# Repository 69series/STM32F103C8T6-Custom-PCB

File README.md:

# STM32F103C8T6 Custom PCB

A custom-designed 2-layer development board built around the STM32F103C8T6 (Arm Cortex-M3), featuring USB, UART, I2C, and SWD interfaces. Designed from schematic to manufacturing files in KiCad, inspired by Phil's Lab's PCB design tutorials.

## Table of Contents

- [Overview](#overview)
- [Features](#features)
- [Schematic](#schematic)
- [PCB Layout](#pcb-layout)
- [Pin Configuration](#pin-configuration)
- [Programming the Board](#programming-the-board)
- [Bill of Materials](#bill-of-materials)
- [Manufacturing Files](#manufacturing-files)
- [Design Decisions](#design-decisions)
- [Future Improvements](#future-improvements)
- [License](#license)

## Overview

This repository documents the complete design process of a custom STM32F103C8T6-based PCB, from schematic capture through PCB layout to manufacturing-ready Gerber files. The project was built as a hands-on learning exercise in embedded hardware design, covering power regulation, USB connectivity, debug/programming interfaces, and signal integrity considerations on a 2-layer board.

## Features

- **MCU:** STM32F103C8T6 (Arm Cortex-M3, 72MHz, 64KB Flash, 20KB RAM)
- **USB 2.0 Full-Speed** connectivity via onboard Micro USB-B connector
- **Three programming/flashing methods:**
  - SWD (Serial Wire Debug) via ST-Link for flashing + live debugging
  - UART bootloader (via broken-out USART1 header)
  - USB DFU bootloader (native USB, no extra hardware required)
- **I2C2 interface** broken out via header for external sensors/peripherals
- **UART1 interface** broken out via header for serial communication/debugging
- **Manual BOOT0 selector switch** for toggling between application and bootloader mode
- **Onboard 3.3V regulation** via AMS1117-3.3 LDO from USB VBUS
- **16MHz crystal oscillator** with calculated load capacitance for accurate clock generation
- **Dedicated analog supply (VDDA)** isolated via ferrite bead for clean ADC performance
- **Solid ground plane** (bottom layer) with thermal-relief pad connections for reliable hand-soldering
- **4x mounting holes** for enclosure/standoff compatibility

## Schematic

The schematic is organized into four functional blocks: power supply, microcontroller core, USB circuitry, and external interface headers.

### Power Supply

- VBAT and all VDD pins are individually decoupled with 100nF capacitors, placed close to each pin to minimize trace inductance and provide a low-impedance path for high-frequency switching noise.
- A 10µF bulk capacitor sits in parallel to handle larger transient current demands.
- VDDA (analog supply) is isolated from the digital 3.3V rail using a 120Ω ferrite bead, preventing digital switching noise from corrupting ADC readings. Three additional decoupling capacitors support this analog rail.
- A AMS1117-3.3 LDO regulates incoming USB VBUS (5V) down to a clean 3.3V rail for the entire board.

### Reset and Boot Configuration

- **NRST** is decoupled with a 100nF capacitor to filter transient noise; no manual reset switch is present in this revision (see [Future Improvements](#future-improvements)).
- **BOOT0** is pulled low through a 10kΩ resistor by default (normal application boot), with a SPDT switch (SW1) allowing manual selection of bootloader mode for flashing.

### Oscillator

- A 16MHz crystal (Y1) provides the system clock, with load capacitors (C10, C11) calculated from the crystal's specified load capacitance, accounting for PCB trace and pin stray capacitance.

### Communication Interfaces

- **USART1** broken out to a 4-pin header (GND, RX, TX, 3.3V) for general-purpose serial communication.
- **I2C2** (SCL/SDA) broken out to a 4-pin header, with 1.5kΩ pull-up resistors on both lines (required since I2C is an open-drain bus).

### USB Circuitry

- Micro USB-B connector provides VBUS for power and D+/D- for USB Full-Speed data.
- D+ is pulled high through a 1.5kΩ resistor, signaling to the host that this is a Full-Speed USB device during enumeration.

### Debug Interface

- SWD (SWDIO, SWCLK) broken out to a 4-pin header (GND, CLK, IO, 3.3V) for programming and live debugging via ST-Link.

## PCB Layout

The board is a 2-layer design (F.Cu / B.Cu) measuring 41.5mm x 33mm, laid out in KiCad.

### Layer Stack

| Layer | Purpose |
|---|---|
| F.Cu (Top) | Signal routing, component placement |
| B.Cu (Bottom) | Solid ground plane (filled zone) |

### Trace Widths

| Net Type | Width | Rationale |
|---|---|---|
| Signal (I2C, UART, GPIO) | 0.3mm | Standard for logic-level signals; current is negligible, width chosen for routability |
| Power / Ground | 0.5mm | Comfortable margin above required ampacity (board draws well under 200mA) |

### Ground Plane Configuration

- **Fill zone:** B.Cu layer, solid ground pour
- **Clearance:** 0.3mm
- **Minimum width:** 0.25mm
- **Pad connection:** Thermal relief (both gap and spoke width = 0.5mm) — chosen over solid/direct connection to keep pads hand-solderable without excessive heat sinking into the copper pour

### Via Sizing

- **Standard vias:** 0.7mm
- **3.3V power vias:** 0.75mm

Via sizes were chosen conservatively (larger than minimum fab capability) to prioritize manufacturing reliability and ease of hand-soldering/rework over board density, appropriate for a learning-focused first PCB project.

### Layout Considerations

- **UART and USB separation:** USART1 was deliberately routed to the top-side header (PB6/PB7) rather than its default pins (PA9/PA10), which sit immediately adjacent to the USB D+/D- lines (PA11/PA12). This reduces the risk of crosstalk between the UART signals and the USB differential pair.
- **Decoupling capacitor placement:** All decoupling capacitors are placed as close as possible to their respective VDD/VSS pin pairs to minimize loop inductance.
- **USB differential pair routing:** D+/D- are routed as a tight, closely-coupled pair into the host detection pull-up network before reaching the MCU.
- **Regulator copper area:** The AMS1117 (U2) is given adjacent copper pour on the 3.3V net to assist with passive heat dissipation.

## Pin Configuration

| Function | Pin(s) | Notes |
|---|---|---|
| USART1 (TX/RX) | PB6 (TX), PB7 (RX) | Moved from default PA9/PA10 to avoid proximity to USB lines |
| I2C2 (SCL/SDA) | PB10 (SCL), PB11 (SDA) | 1.5kΩ pull-ups on both lines |
| USB | PA11 (D-), PA12 (D+) | D+ pulled high via 1.5kΩ for Full-Speed device detection |
| SWD | PA13 (SWDIO), PA14 (SWCLK) | Programming and debugging via ST-Link |
| BOOT0 | Pin 44 | Pulled low via 10kΩ by default; SPDT switch allows manual high selection |
| NRST | Pin 7 | Decoupled with 100nF capacitor; no manual reset switch in this revision |
| OSC_IN / OSC_OUT | PD0, PD1 | 16MHz external crystal with calculated load capacitors |
| VDD / VSS | Multiple pins | Individually decoupled with 100nF capacitors + 10µF bulk capacitor |
| VDDA / VSSA | Analog supply pins | Isolated via 120Ω ferrite bead from digital 3.3V rail |

## Programming the Board

This board supports three independent methods for flashing firmware, offering flexibility depending on available hardware.

### Method 1: SWD (recommended for development)

**Requires:** ST-Link V2 programmer/debugger

1. Connect ST-Link to the SWD header (GND, CLK, IO, 3.3V)
2. Flash and debug directly from STM32CubeIDE, or via STM32CubeProgrammer
3. Supports full live debugging — breakpoints, register/variable inspection, step execution

This is the only method that supports real-time debugging, not just flashing.

### Method 2: UART Bootloader

**Requires:** USB-to-TTL serial adapter

1. Set **BOOT0 = HIGH** using SW1
2. Connect the adapter to the UART1 header (GND, RX, TX, 3.3V) — cross TX/RX between board and adapter
3. Power cycle the board (no manual reset switch in this revision)
4. Flash using STM32CubeProgrammer (UART connection mode) or compatible tools
5. Set **BOOT0 = LOW**, power cycle again to boot the new application

### Method 3: USB DFU Bootloader

**Requires:** Micro USB-B cable only (no extra hardware)

1. Set **BOOT0 = HIGH** using SW1
2. Connect the board via USB — it enumerates as a DFU device
3. **Windows only:** install a WinUSB driver using [Zadig](https://zadig.akeo.ie/) (one-time setup)
4. Flash using `dfu-util` or STM32CubeProgrammer (USB connection mode):
`dfu-util -a 0 -s 0x08000000:leave -D firmware.bin`
5. Set **BOOT0 = LOW**, power cycle to boot the new application

> **Note:** Unlike boards with an onboard USB-to-serial bridge (e.g. ESP32 dev boards), this design requires manual BOOT0/reset toggling for every flash cycle, since there is no automatic reset circuitry. See [Future Improvements](#future-improvements) for a planned revision addressing this.

## Bill of Materials

| Ref | Qty | Value / Part | Footprint | Description |
|---|---|---|---|---|
| U1 | 1 | STM32F103C8T6 | LQFP-48, 7x7mm, 0.5mm pitch | Arm Cortex-M3 MCU, 64KB Flash, 20KB RAM, 72MHz |
| U2 | 1 | AMS1117-3.3 | SOT-223-3 | 1A LDO regulator, 3.3V fixed output |
| Y1 | 1 | 16MHz crystal | 3225 SMD (3.2x2.5mm) | 4-pin crystal, GND on pins 2 & 4 |
| J1 | 1 | USB Micro-B | Würth 629105150521 | USB connector for power + data |
| J2, J3, J4 | 3 | Conn_01x04_Pin | 2.54mm pin header, 1x04 | UART, SWD, and I2C breakout headers |
| SW1 | 1 | SW_SPDT | SMD SPDT (PCM12) | BOOT0 mode selector switch |
| D1 | 1 | LED (Red) | 0603 | Power/status indicator |
| FB1 | 1 | 120Ω ferrite bead | 0603 | VDDA noise isolation |
| C1, C2, C3, C4, C9 | 5 | 100nF | 0402 | Decoupling capacitors |
| C5 | 1 | 10µF | 0603 | Bulk decoupling capacitor |
| C6 | 1 | 10nF | 0402 | Decoupling capacitor |
| C7, C8 | 2 | 1µF | 0402 | VDDA decoupling capacitors |
| C10, C11 | 2 | 10pF | 0402 | Crystal load capacitors |
| C12, C13 | 2 | 22µF | 0805 | USB/regulator bulk capacitors |
| R1 | 1 | 10kΩ | 0402 | BOOT0 pulldown resistor |
| R2 | 1 | 1.5kΩ | 0402 | USB D+ pull-up resistor |
| R3, R4, R5 | 3 | 1.5kΩ | 0402 (hand-solder pad) | I2C2 SCL/SDA pull-ups |

**Total component count:** 17 unique references, 30 individual parts

Full machine-readable BOM available at [`manufacturing/STM32F103C8T6.csv`](manufacturing/STM32F103C8T6.csv).

## Manufacturing Files

All files required to fabricate and assemble this board are available in the [`manufacturing/`](manufacturing/) folder.

| File | Purpose |
|---|---|
| `STM32F103C8T6-F_Cu.gbr` | Top copper layer |
| `STM32F103C8T6-B_Cu.gbr` | Bottom copper layer (ground plane) |
| `STM32F103C8T6-F_Mask.gbr` | Top soldermask |
| `STM32F103C8T6-B_Mask.gbr` | Bottom soldermask |
| `STM32F103C8T6-F_Paste.gbr` | Top solder paste (for SMT assembly) |
| `STM32F103C8T6-B_Paste.gbr` | Bottom solder paste |
| `STM32F103C8T6-F_Silkscreen.gbr` | Top silkscreen |
| `STM32F103C8T6-B_Silkscreen.gbr` | Bottom silkscreen |
| `STM32F103C8T6-Edge_Cuts.gbr` | Board outline |
| `STM32F103C8T6.drl` | Drill file (holes and vias) |
| `STM32F103C8T6.csv` | Component placement / position file |
| `STM32F103C8T6-all-pos.csv` | Full pick-and-place file |

### Ordering this board

1. Compress the entire `manufacturing/` folder into a `.zip`
2. Upload to any PCB fabrication service (e.g. JLCPCB, PCBWay, OSH Park)
3. Standard 2-layer specifications apply (1.6mm board thickness, 1oz copper — adjust if your fab defaults differ)
4. For SMT assembly service, the position files (`.csv`) and BOM can be supplied alongside the Gerbers

## Design Decisions

This section documents the reasoning behind key design choices, beyond just "what" was implemented.

### Power Integrity

- **Per-pin decoupling over shared capacitors:** Each VDD pin has its own dedicated 100nF capacitor placed as close as possible, rather than sharing fewer capacitors across multiple pins. Trace length between a capacitor and a pin adds inductance, which degrades high-frequency decoupling effectiveness — shorter paths mean cleaner suppression of switching noise.
- **Bulk + decoupling capacitor pairing:** The 10µF bulk capacitor and 100nF decoupling capacitors serve different roles — the bulk capacitor handles slower, larger transient current demands, while the smaller capacitors filter high-frequency noise. Neither alone is sufficient.
- **Analog supply isolation:** VDDA is separated from the digital 3.3V rail using a ferrite bead rather than a simple trace connection. Digital switching noise on VDD would otherwise couple directly into the ADC's reference supply, degrading analog measurement accuracy.

### Signal Routing

- **UART relocated away from USB:** USART1 was moved from its default pins (PA9/PA10) to PB6/PB7 specifically because the default pins sit immediately adjacent to the USB differential pair (PA11/PA12) on the physical package. This reduces the risk of crosstalk between UART signaling and the sensitive USB data lines.
- **USB differential pair routing:** D+/D- are routed as a closely-coupled pair to maintain consistent characteristic impedance, with the pull-up resistor placed close to the connector before the signals reach the MCU.

### Manufacturing and Assembly Tradeoffs

- **Thermal relief over solid ground connection:** The bottom-layer ground plane connects to pads via thermal relief (spoked) rather than a direct solid fill. A pad fused directly into a large copper pour sinks heat extremely fast, making hand-soldering difficult or impossible. Thermal relief trades a small amount of electrical/thermal performance for practical assembly feasibility.
- **Conservative via sizing:** 0.7mm/0.75mm vias were chosen deliberately larger than the minimum size most fabs support. This prioritizes manufacturing yield and tolerance margin over board density — an appropriate tradeoff for a first PCB design where reliability of the physical board mattered more than compactness.

### Programming and Debug Strategy

- **Three independent flashing paths:** Rather than relying on a single programming method, the board supports SWD, UART bootloader, and USB DFU. SWD is the only method offering live debugging; the other two provide flashing-only fallback paths requiring no specialized programmer hardware. This redundancy was a deliberate choice to maximize flexibility, since SWD requires an external ST-Link, which may not always be on hand.

## Future Improvements

- **Manual reset button:** Add a pushbutton across NRST and GND (alongside the existing decoupling capacitor) to allow manual reset without power-cycling the board.
- **Automatic flashing via USB-UART bridge:** Add a CP2102/CH340-style USB-to-UART bridge chip wired to UART1, combined with a DTR/RTS-driven transistor circuit controlling NRST and BOOT0. This would replicate the auto-reset behavior seen on boards like ESP32 dev kits, removing the need to manually toggle BOOT0 and power-cycle the board for every UART flash.
- **Status LEDs:** Add dedicated LEDs for power and a user-controllable GPIO indicator, beyond the current single power/status LED.
- **Reverse polarity / ESD protection:** Add protection diodes on the USB VBUS line and ESD suppression on the D+/D- lines for improved robustness in real-world use.
- **Castellated edge or header-based expansion:** Consider exposing additional unused GPIOs (currently marked as no-connect in the schematic) via a header for future peripheral expansion.

## License

This project is licensed under the MIT License — see the [LICENSE](LICENSE) file for details.

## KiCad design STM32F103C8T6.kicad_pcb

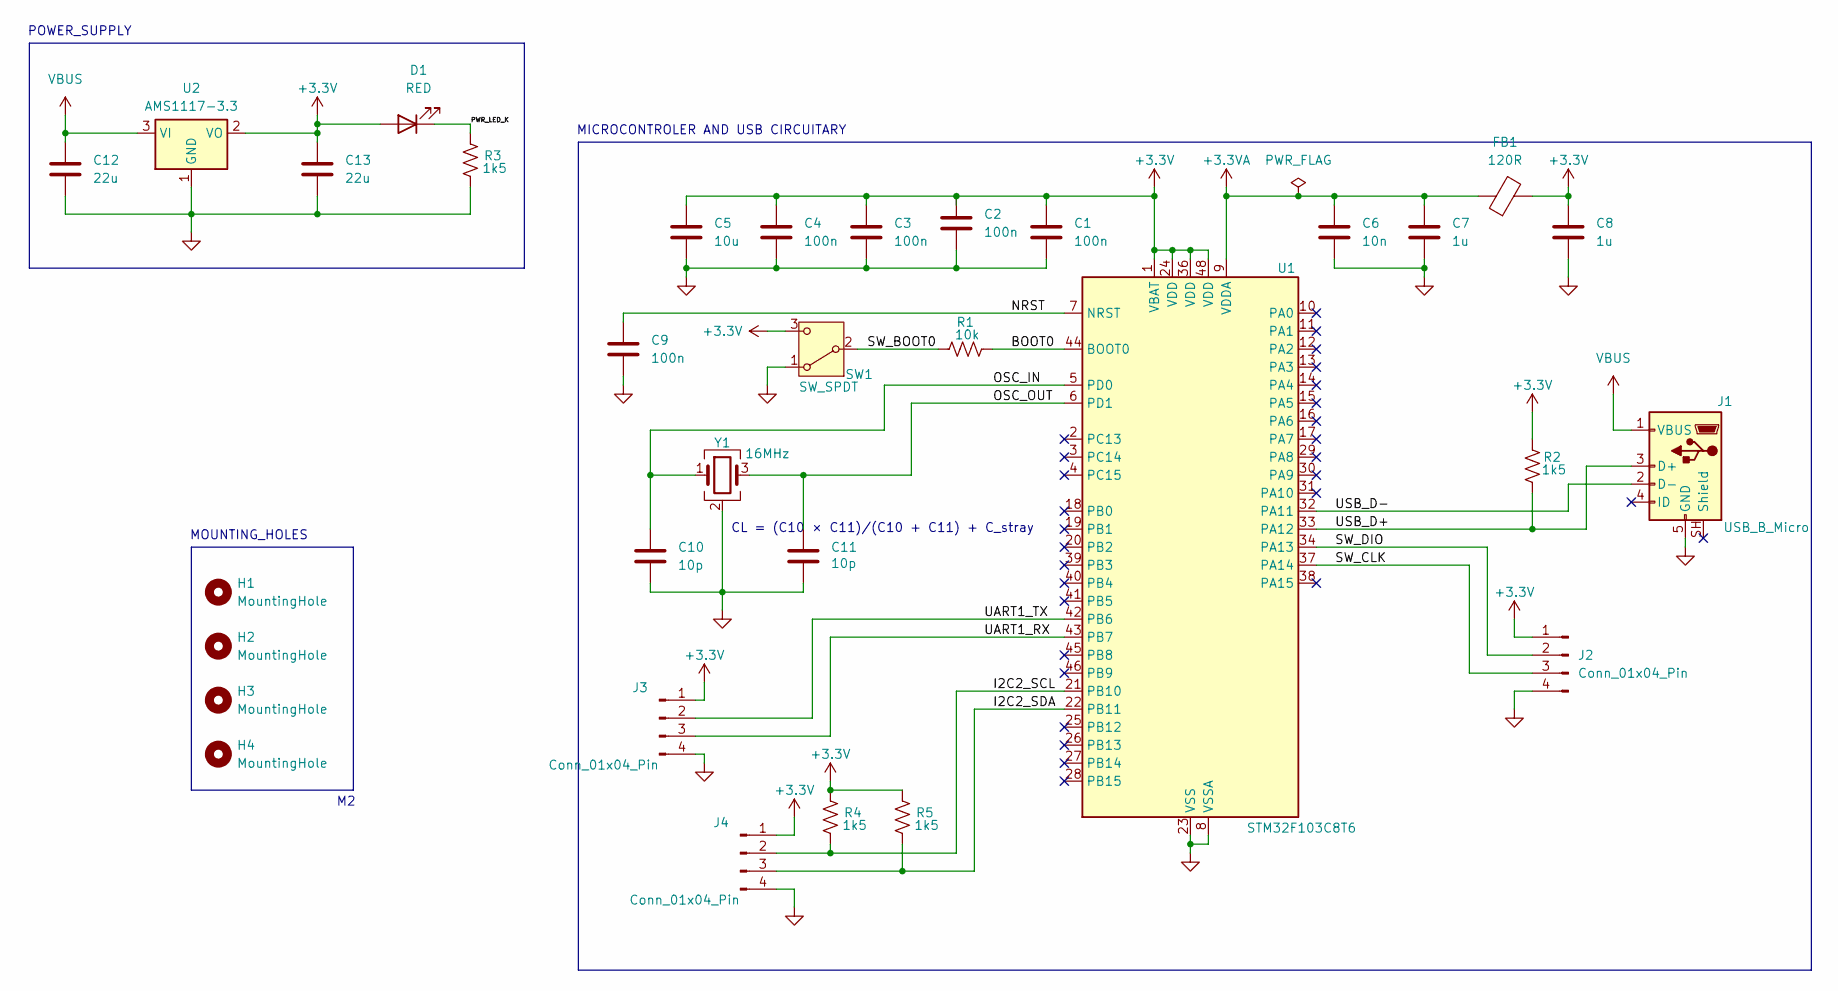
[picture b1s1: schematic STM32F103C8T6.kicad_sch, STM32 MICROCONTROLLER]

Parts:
C1, C2, C3, C4, C9: 100n; C_0402_1005Metric
C5: 10u; C_0603_1608Metric
C6: 10n; C_0402_1005Metric
C7, C8: 1u; C_0402_1005Metric
C10, C11: 10p; C_0402_1005Metric
C12, C13: 22u; C_0805_2012Metric
D1: RED; LED_0603_1608Metric
FB1: 120R; L_0603_1608Metric
H1, H2, H3, H4: MountingHole; MountingHole_2.2mm_M2
J1: USB_B_Micro; USB_Micro-B_Wuerth_629105150521
J2, J3, J4: Conn_01x04_Pin; PinHeader_1x04_P2.54mm_Vertical
R1: 10k; R_0402_1005Metric
R2: 1k5; R_0402_1005Metric
R3, R4, R5: 1k5; R_0402_1005Metric_Pad0.72x0.64mm_HandSolder
SW1: SW_SPDT; SW_SPDT_PCM12
U1: STM32F103C8T6; LQFP-48_7x7mm_P0.5mm
U2: AMS1117-3.3; SOT-223-3_TabPin2
Y1: 16MHz; Crystal_SMD_3225-4Pin_3.2x2.5mm

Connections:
+3.3V: C1.1, C2.1, C3.1, C4.1, C5.1, C8.1, C13.1, D1.2 (A), FB1.2, J2.1, J3.1, J4.1, R2.1, R4.1, R5.1, SW1.3 (C), U1.1 (VBAT), U1.24 (VDD), U1.36 (VDD), U1.48 (VDD), U2.2 (VO)
+3.3VA: C6.1, C7.1, FB1.1, U1.9 (VDDA)
/BOOT0: R1.2, U1.44 (BOOT0)
/I2C2_SCL: J4.2, R4.2, U1.21 (PB10)
/I2C2_SDA: J4.3, R5.2, U1.22 (PB11)
/NRST: C9.1, U1.7 (NRST)
/OSC_IN: C10.1, U1.5 (PD0), Y1.1
/OSC_OUT: C11.2, U1.6 (PD1), Y1.3
/PWR_LED_K: D1.1 (K), R3.1
/SW_BOOT0: R1.1, SW1.2 (B)
/SW_CLK: J2.3, U1.37 (PA14)
/SW_DIO: J2.2, U1.34 (PA13)
/UART1_RX: J3.3, U1.43 (PB7)
/UART1_TX: J3.2, U1.42 (PB6)
/USB_D+: J1.3 (D+), R2.2, U1.33 (PA12)
/USB_D-: J1.2 (D-), U1.32 (PA11)
GND: C1.2, C2.2, C3.2, C4.2, C5.2, C6.2, C7.2, C8.2, C9.2, C10.2, C11.1, C12.2, C13.2, J1.5 (GND), J2.4, J3.4, J4.4, R3.2, SW1.1 (A), U1.8 (VSSA), U1.23 (VSS), U1.35 (VSS), U1.47 (VSS), U2.1 (GND), Y1.2 (G), Y1.4 (G)
VBUS: C12.1, J1.1 (VBUS), U2.3 (VI)

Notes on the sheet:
CL = (C10 × C11)/(C10 + C11) + C_stray
POWER_SUPPLY
MOUNTING_HOLES
MICROCONTROLER AND USB CIRCUITARY

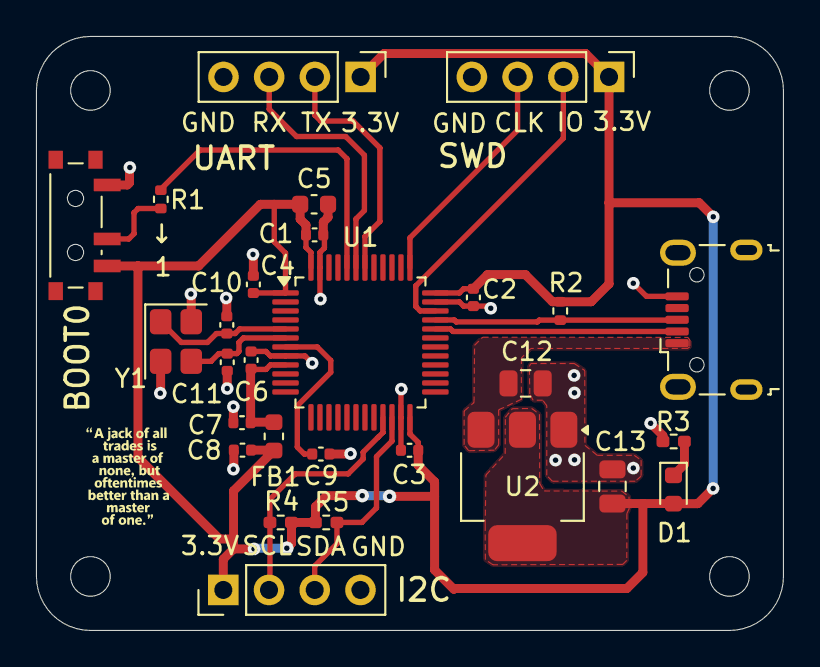
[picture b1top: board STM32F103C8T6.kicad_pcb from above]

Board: 2 copper layers, 41.5 x 33.0 mm, 32 parts (0 on the bottom side), 18 nets.

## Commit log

2026-06-22 Initial commit: STM32F103C8T6 schematic, PCB layout, and manufacturing files
2026-06-22 add readme
2026-06-22 Add README documentation with schematic, PCB layout images, and design rationale

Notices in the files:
README.md:
License: MIT
